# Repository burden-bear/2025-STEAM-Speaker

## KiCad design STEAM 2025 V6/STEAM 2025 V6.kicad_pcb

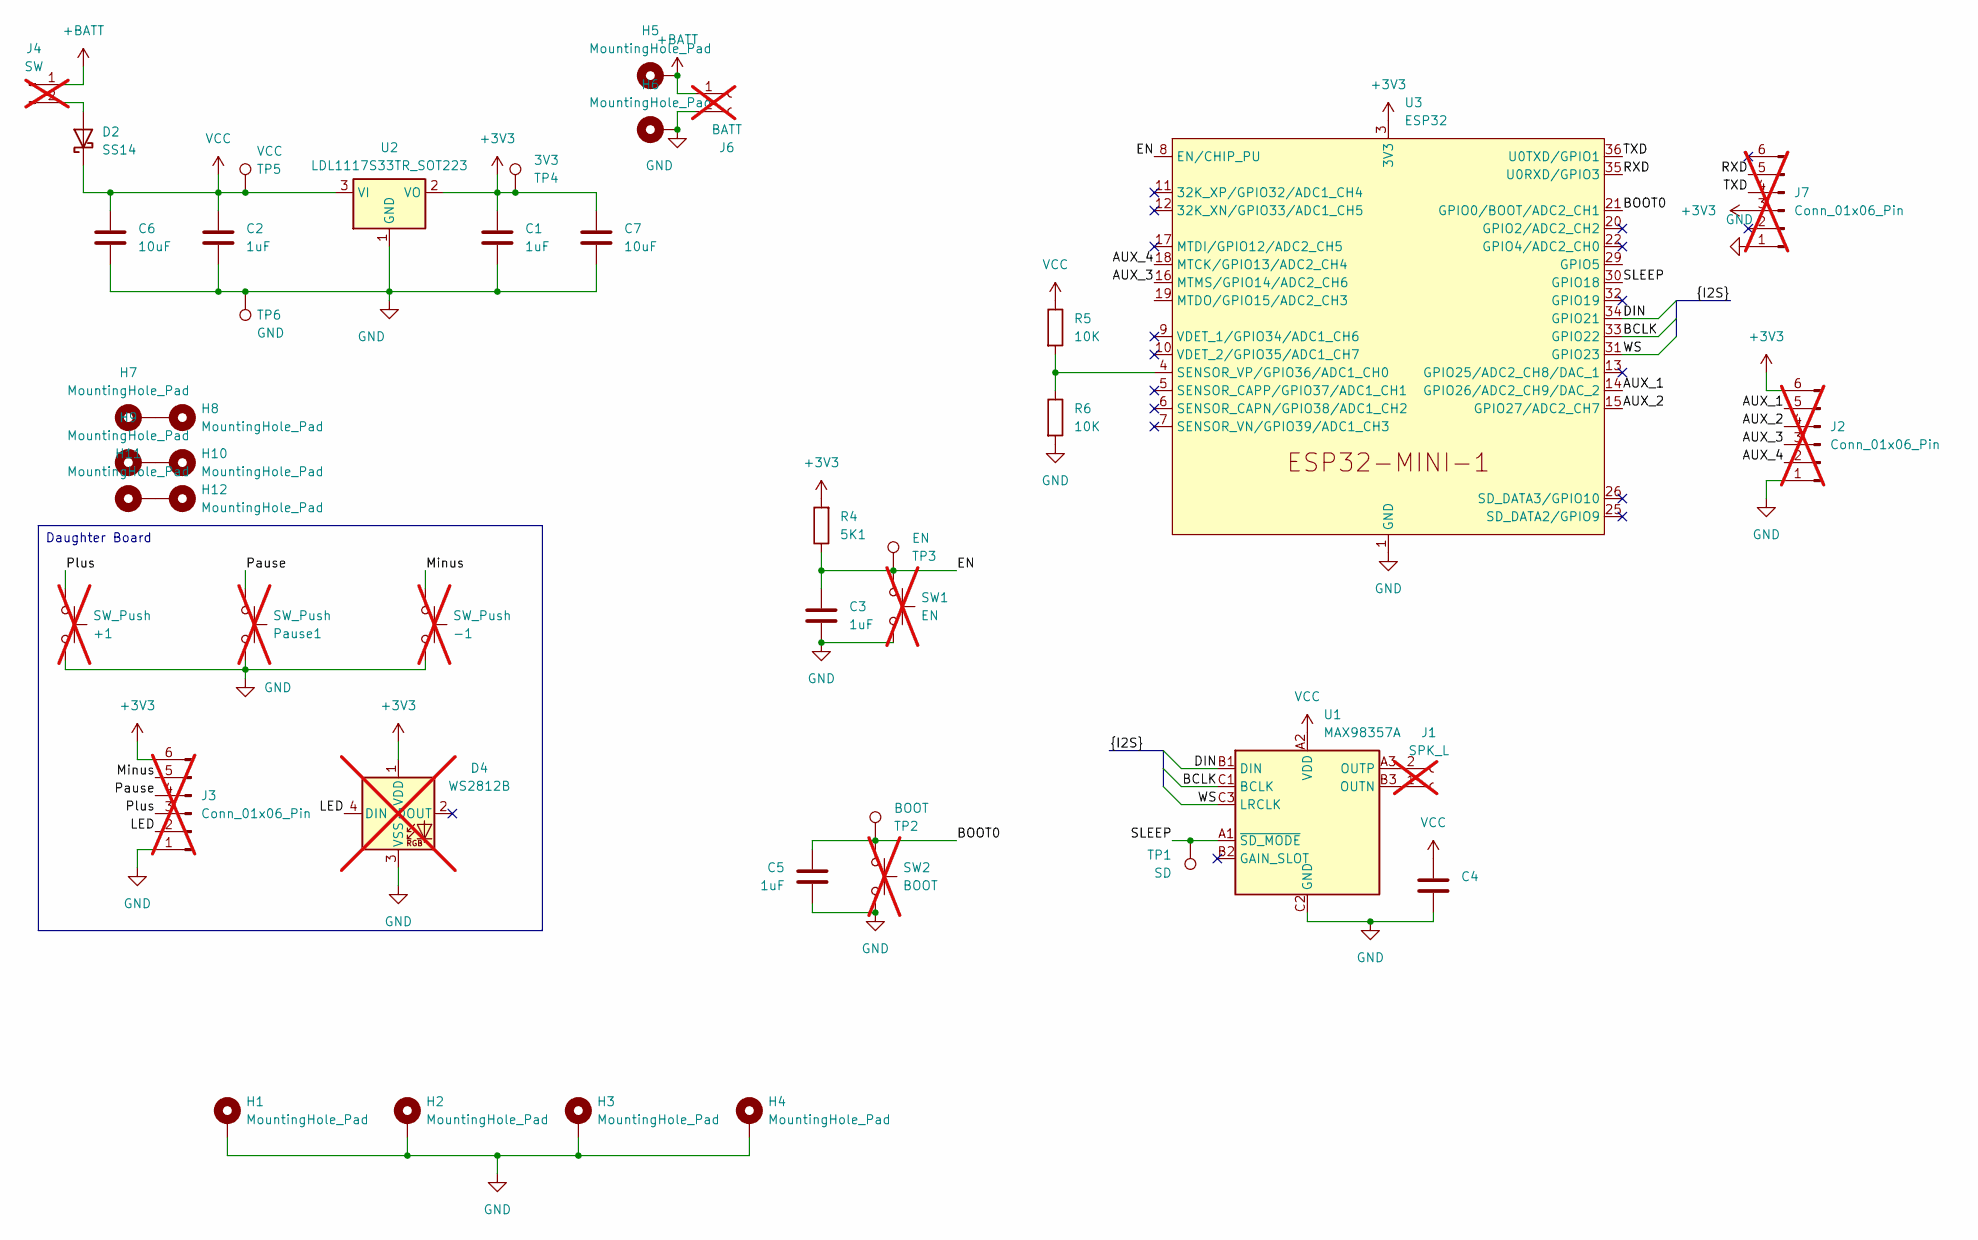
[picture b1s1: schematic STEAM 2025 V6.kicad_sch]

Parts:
+1: SW_Push; SW_PUSH_6mm_H5mm; not fitted
-1: SW_Push; SW_PUSH_6mm_H5mm; not fitted
C1, C2, C3, C5: 1uF; C_0402_1005Metric; LCSC C52923
C4: 0.1uF; C_0402_1005Metric; LCSC C1525
C6, C7: 10uF; C_0603_1608Metric; LCSC C96446
D2: SS14; D_SMA; LCSC C2480
D4: WS2812B; 2812b 60pm; not fitted
H1, H2, H3, H4: MountingHole_Pad; MountingHole_3.2mm_M3_DIN965_Pad
H5, H6, H7, H8, H9, H10, H11, H12: MountingHole_Pad; MountingHole_2.7mm_Slot
J1: SPK_L; PinHeader_1x02_P2.54mm_Vertical; part C27910; not fitted
J2, J3, J7: Conn_01x06_Pin; PinHeader_1x06_P2.54mm_Vertical; not fitted
J4: SW; PinHeader_1x02_P2.54mm_Vertical; not fitted
J6: BATT; PinHeader_1x02_P2.54mm_Vertical; part C27910; not fitted
Pause1: SW_Push; SW_PUSH_6mm_H5mm; not fitted
R4: 5K1; R_0402_1005Metric; LCSC C105872
R5, R6: 10K; R_0402_1005Metric; LCSC C60490
SW1: EN; SW_PUSH_6mm_H5mm; not fitted
SW2: BOOT; SW_PUSH_6mm_H5mm; not fitted
TP1: SD; TestPoint_Pad_D2.0mm
TP2: BOOT; TestPoint_Pad_D2.0mm
TP3: EN; TestPoint_Pad_D2.0mm
TP4: 3V3; TestPoint_Pad_D2.0mm
TP5: VCC; TestPoint_Pad_D2.0mm
TP6: GND; TestPoint_Pad_D2.0mm
U1: MAX98357A; WLP-9_1.448x1.468mm_Layout3x3_P0.4mm_Ball0.27mm_Pad0.25mm; LCSC C2682619
U2: LDL1117S33TR_SOT223; SOT-223-3_TabPin2; LCSC C435835
U3: ESP32; ESP32-MINI-1; LCSC C3013933

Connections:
+3V3: C1.1, C7.1, D4.1 (VDD), J2.6, J3.6, J7.3, R4.2, TP4.1, U2.2 (VO), U3.3 (3V3)
+BATT: H5.1, J4.1, J6.1
/AUX_1: J2.5, U3.14 (GPIO26/ADC2_CH9/DAC_2)
/AUX_2: J2.4, U3.15 (GPIO27/ADC2_CH7)
/AUX_3: J2.3, U3.16 (MTMS/GPIO14/ADC2_CH6)
/AUX_4: J2.2, U3.18 (MTCK/GPIO13/ADC2_CH4)
/BCLK: U1.C1 (BCLK), U3.33 (GPIO22)
/BOOT0: C5.1, SW2.1, TP2.1, U3.21 (GPIO0/BOOT/ADC2_CH1)
/DIN: U1.B1 (DIN), U3.34 (GPIO21)
/EN: C3.1, R4.1, SW1.1, TP3.1, U3.8 (EN/CHIP_PU)
/LED: D4.4 (DIN), J3.2
/Minus: -1.2, J3.5
/Pause: J3.4, Pause1.2
/Plus: +1.2, J3.3
/RXD: J7.5, U3.35 (U0RXD/GPIO3)
/SLEEP: TP1.1, U1.A1 (~SD_MODE), U3.30 (GPIO18)
/TXD: J7.4, U3.36 (U0TXD/GPIO1)
/WS: U1.C3 (LRCLK), U3.31 (GPIO23)
GND: +1.1, -1.1, C1.2, C2.2, C3.2, C4.2, C5.2, C6.2, C7.2, D4.3 (VSS), H1.1, H2.1, H3.1, H4.1, H6.1, J2.1, J3.1, J6.2, J7.1, Pause1.1, R6.2, SW1.2, SW2.2, TP6.1, U1.C2 (GND), U2.1 (GND), U3.1 (GND), U3.2 (GND), U3.27 (GND), U3.38 (GND), U3.39 (GND), U3.40 (GND), U3.41 (GND), U3.42 (GND), U3.43 (GND), U3.44 (GND), U3.45 (GND), U3.46 (GND), U3.47 (GND), U3.48 (GND), U3.49 (GND), U3.50 (GND), U3.51 (GND), U3.52 (GND), U3.53 (GND), U3.54 (GND), U3.55 (GND); also elsewhere on the board
unnamed: D2.2 (A), J4.2
unnamed: H7.1, H8.1
unnamed: H9.1, H10.1
unnamed: H11.1, H12.1
unnamed: J1.1, U1.B3 (OUTN)
unnamed: J1.2, U1.A3 (OUTP)
unnamed: R5.2, R6.1, U3.4 (SENSOR_VP/GPIO36/ADC1_CH0)
VCC: C2.1, C4.1, C6.1, D2.1 (K), R5.1, TP5.1, U1.A2 (VDD), U2.3 (VI)

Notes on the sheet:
Daughter Board

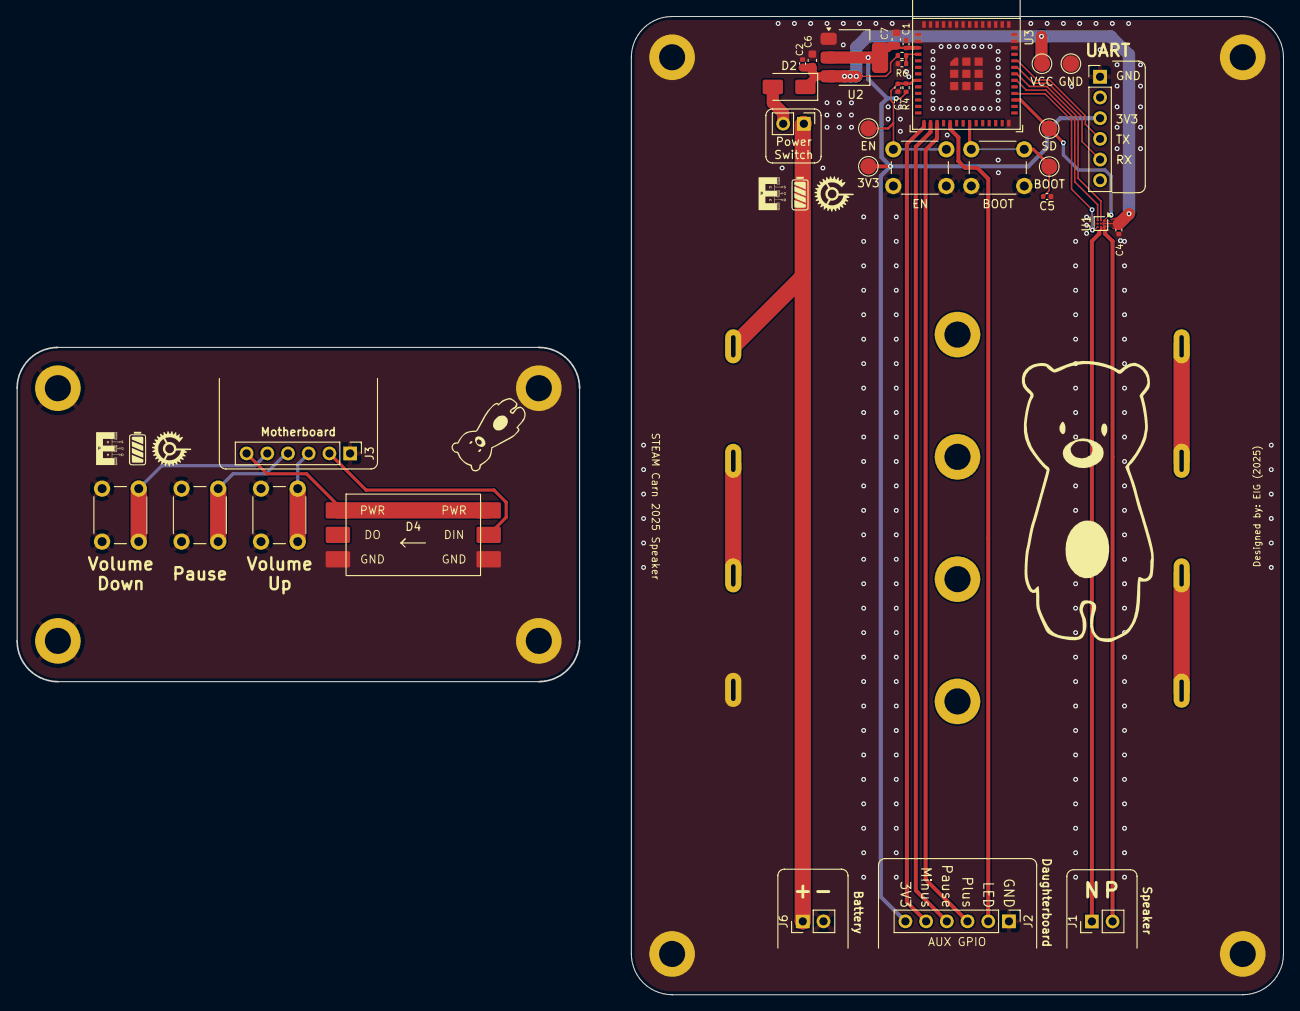
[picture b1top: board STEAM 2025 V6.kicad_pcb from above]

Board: 2 copper layers, 155.3 x 119.8 mm, 46 parts (0 on the bottom side), 27 nets.

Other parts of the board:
H2#2, H4#2: MountingHole_Pad; MountingHole_3.2mm_M3_DIN965_Pad

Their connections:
GND: H2#2.1, H4#2.1; also elsewhere on the board

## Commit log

2025-07-20 Add files via upload
    Manufactured, pending testing
